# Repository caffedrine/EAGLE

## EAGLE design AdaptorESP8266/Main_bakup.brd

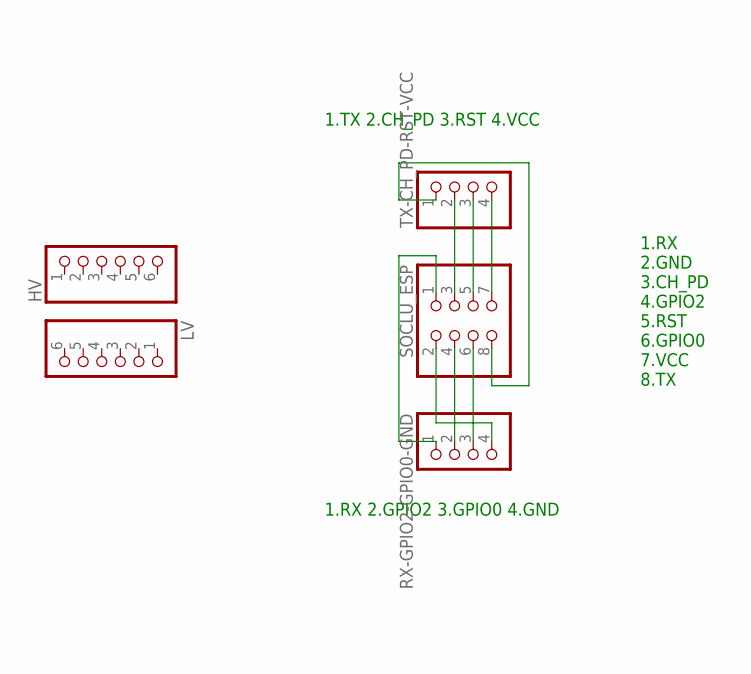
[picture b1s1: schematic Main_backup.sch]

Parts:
HV: PINHD-1X6; 1X06
LV: PINHD-1X6; 1X06
RX-GPIO2-GPIO0-GND: PINHD-1X4; 1X04
SOCLU_ESP: PINHD-2X4; 2X04
TX-CH_PD-RST-VCC: PINHD-1X4; 1X04

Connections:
unnamed: SOCLU_ESP.7, TX-CH_PD-RST-VCC.4
unnamed: SOCLU_ESP.5, TX-CH_PD-RST-VCC.3
unnamed: SOCLU_ESP.3, TX-CH_PD-RST-VCC.2
unnamed: SOCLU_ESP.8, TX-CH_PD-RST-VCC.1
unnamed: RX-GPIO2-GPIO0-GND.1, SOCLU_ESP.1
unnamed: RX-GPIO2-GPIO0-GND.4, SOCLU_ESP.2
unnamed: RX-GPIO2-GPIO0-GND.3, SOCLU_ESP.6
unnamed: RX-GPIO2-GPIO0-GND.2, SOCLU_ESP.4

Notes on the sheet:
1.RX 2.GND 3.CH_PD 4.GPIO2 5.RST 6.GPIO0 7.VCC 8.TX
1.TX 2.CH_PD 3.RST 4.VCC
1.RX 2.GPIO2 3.GPIO0 4.GND

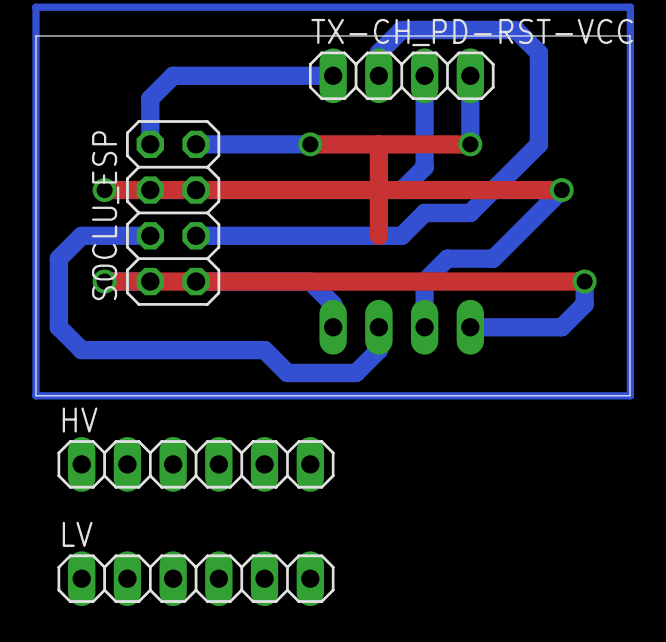
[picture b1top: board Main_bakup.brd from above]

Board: 2 copper layers, 33.0 x 20.0 mm, 5 parts (1 on the bottom side), 8 nets.

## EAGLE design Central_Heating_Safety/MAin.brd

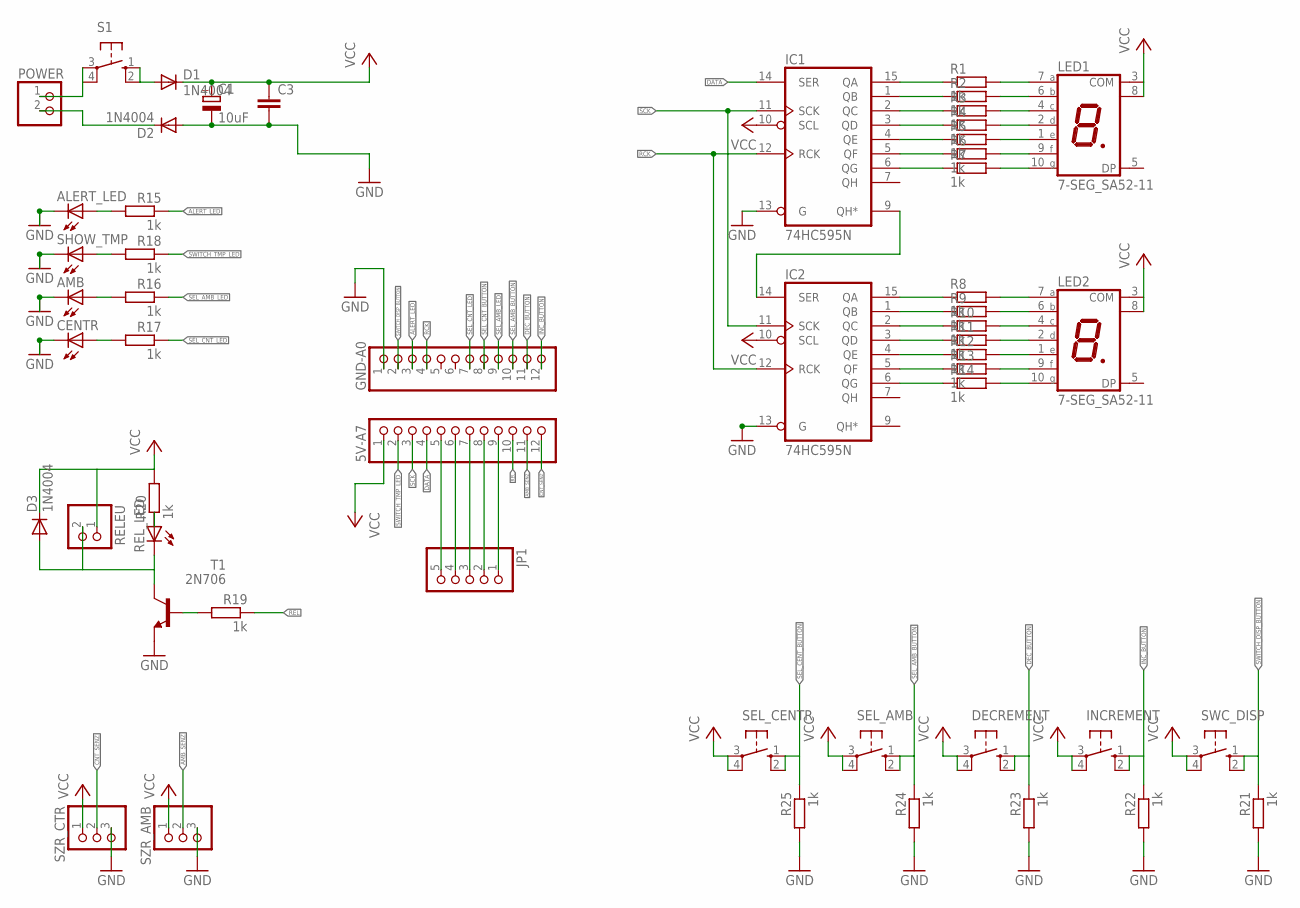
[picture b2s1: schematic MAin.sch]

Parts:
5V-A7: PINHD-1X12; 1X12
ALERT_LED: LED5MM
AMB: LED5MM
C1: 10uF; E2-5
C3: C-EU025-024X044; C025-024X044
CENTR: LED5MM
D1, D2, D3: 1N4004; DO41-10
DECREMENT: 40-XX; B3F-40XX
GND-A0: PINHD-1X12; 1X12
IC1, IC2: 74HC595N; DIL16
INCREMENT: 40-XX; B3F-40XX
JP1: PINHD-1X5; 1X05
LED1, LED2: 7-SEG_SA52-11; SA52-11
POWER: PINHD-1X2; 1X02
R1, R2, R3, R4, R5, R6, R7, R8, R9, R10, R11, R12, R13, R14, R15, R16, R17, R18, R19, R20, R21, R22, R23, R24, R25: 1k; 0309/12
RELEU: PINHD-1X2; 1X02
REL_LED: LED5MM
S1: 10-XX; B3F-10XX
SEL_AMB: 40-XX; B3F-40XX
SEL_CENTR: 40-XX; B3F-40XX
SHOW_TMP: LED5MM
SWC_DISP: 40-XX; B3F-40XX
SZR_AMB: PINHD-1X3; 1X03
SZR_CTR: PINHD-1X3; 1X03
T1: 2N706; TO18

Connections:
ALERT_LED: GND-A0.3, R15.1
AMB_SENZ: 5V-A7.11, SZR_AMB.2
CNT_SENZ: 5V-A7.12, SZR_CTR.2
DATA: 5V-A7.4, IC1.14 (SER)
DEC_BUTTON: DECREMENT.1 (S), DECREMENT.2 (S1), GND-A0.11, R23.1
GND: ALERT_LED.K (C), AMB.K (C), C1.-, C3.2, CENTR.K (C), D2.A, GND-A0.1, IC1.8 (GND), IC1.13 (G), IC2.8 (GND), IC2.13 (G), R21.2, R22.2, R23.2, R24.2, R25.2, SHOW_TMP.K (C), SZR_AMB.3, SZR_CTR.3, T1.1 (E)
INC_BUTTON: GND-A0.12, INCREMENT.1 (S), INCREMENT.2 (S1), R22.1
unnamed: LED1.7 (A), R1.2
unnamed: LED1.6 (B), R2.2
unnamed: LED1.4 (C), R3.2
unnamed: LED1.2 (D), R4.2
unnamed: LED1.1 (E), R5.2
unnamed: LED1.9 (F), R6.2
unnamed: LED1.10 (G), R7.2
unnamed: LED2.7 (A), R8.2
unnamed: LED2.6 (B), R9.2
unnamed: LED2.4 (C), R10.2
unnamed: LED2.2 (D), R11.2
unnamed: LED2.1 (E), R12.2
unnamed: LED2.9 (F), R13.2
unnamed: LED2.10 (G), R14.2
unnamed: IC1.15 (QA), R1.1
unnamed: IC1.1 (QB), R2.1
unnamed: IC1.2 (QC), R3.1
unnamed: IC1.3 (QD), R4.1
unnamed: IC1.4 (QE), R5.1
unnamed: IC1.5 (QF), R6.1
unnamed: IC1.6 (QG), R7.1
unnamed: IC2.15 (QA), R8.1
unnamed: IC2.1 (QB), R9.1
unnamed: IC2.2 (QC), R10.1
unnamed: IC2.3 (QD), R11.1
unnamed: IC2.4 (QE), R12.1
unnamed: IC2.5 (QF), R13.1
unnamed: IC2.6 (QG), R14.1
unnamed: IC1.9 (QH*), IC2.14 (SER)
unnamed: 5V-A7.9, JP1.1
unnamed: 5V-A7.8, JP1.2
unnamed: 5V-A7.7, JP1.3
unnamed: 5V-A7.6, JP1.4
unnamed: 5V-A7.5, JP1.5
unnamed: D1.A, S1.1 (S), S1.2 (S1)
unnamed: POWER.1, S1.3, S1.4 (P1)
unnamed: ALERT_LED.A, R15.2
unnamed: D2.C, POWER.2
unnamed: R20.1, REL_LED.A
unnamed: R19.2, T1.2 (B)
unnamed: AMB.A, R16.2
unnamed: CENTR.A, R17.2
unnamed: R18.2, SHOW_TMP.A
unnamed: D3.A, RELEU.2, REL_LED.K (C), T1.3 (C)
RCK: GND-A0.4, IC1.12 (RCK), IC2.12 (RCK)
REL: 5V-A7.10, R19.1
SCK: 5V-A7.3, IC1.11 (SCK), IC2.11 (SCK)
SEL_AMB_BUTTON: GND-A0.10, R24.1, SEL_AMB.1 (S), SEL_AMB.2 (S1)
SEL_AMB_LED: GND-A0.9, R16.1
SEL_CENT_BUTTON: GND-A0.7, R25.1, SEL_CENTR.1 (S), SEL_CENTR.2 (S1)
SEL_CNT_BUTTON: GND-A0.8
SEL_CNT_LED: R17.1
SWITCH_DISP_BUTTON: GND-A0.2, R21.1, SWC_DISP.1 (S), SWC_DISP.2 (S1)
SWITCH_TMP_LED: 5V-A7.2, R18.1
VCC: 5V-A7.1, C1.+, C3.1, D1.C, D3.C, DECREMENT.3, DECREMENT.4 (P1), IC1.10 (SCL), IC1.16 (VCC), IC2.10 (SCL), IC2.16 (VCC), INCREMENT.3, INCREMENT.4 (P1), LED1.3 (COM), LED1.8 (COM), LED2.3 (COM), LED2.8 (COM), R20.2, RELEU.1, SEL_AMB.3, SEL_AMB.4 (P1), SEL_CENTR.3, SEL_CENTR.4 (P1), SWC_DISP.3, SWC_DISP.4 (P1), SZR_AMB.1, SZR_CTR.1

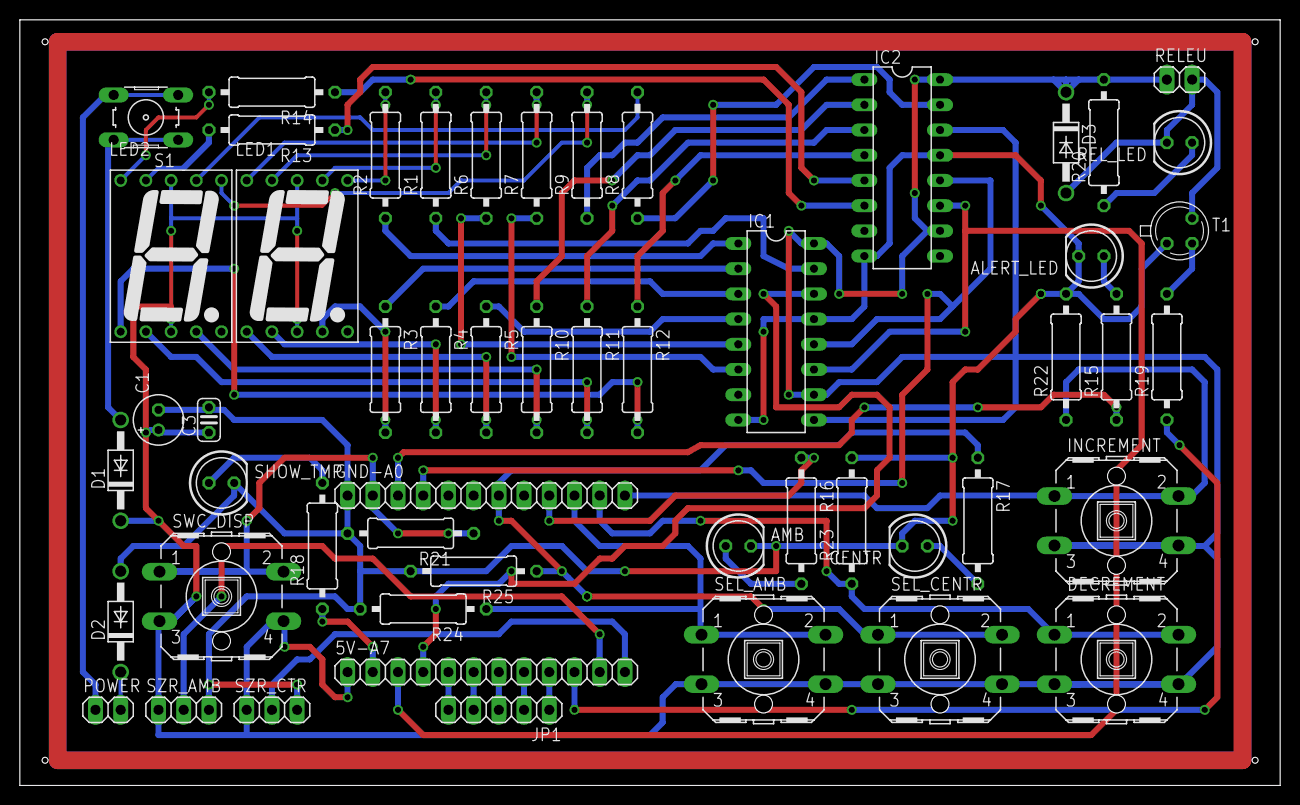
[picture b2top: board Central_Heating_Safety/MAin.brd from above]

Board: 2 copper layers, 127.0 x 77.1 mm, 53 parts (0 on the bottom side), 60 nets.

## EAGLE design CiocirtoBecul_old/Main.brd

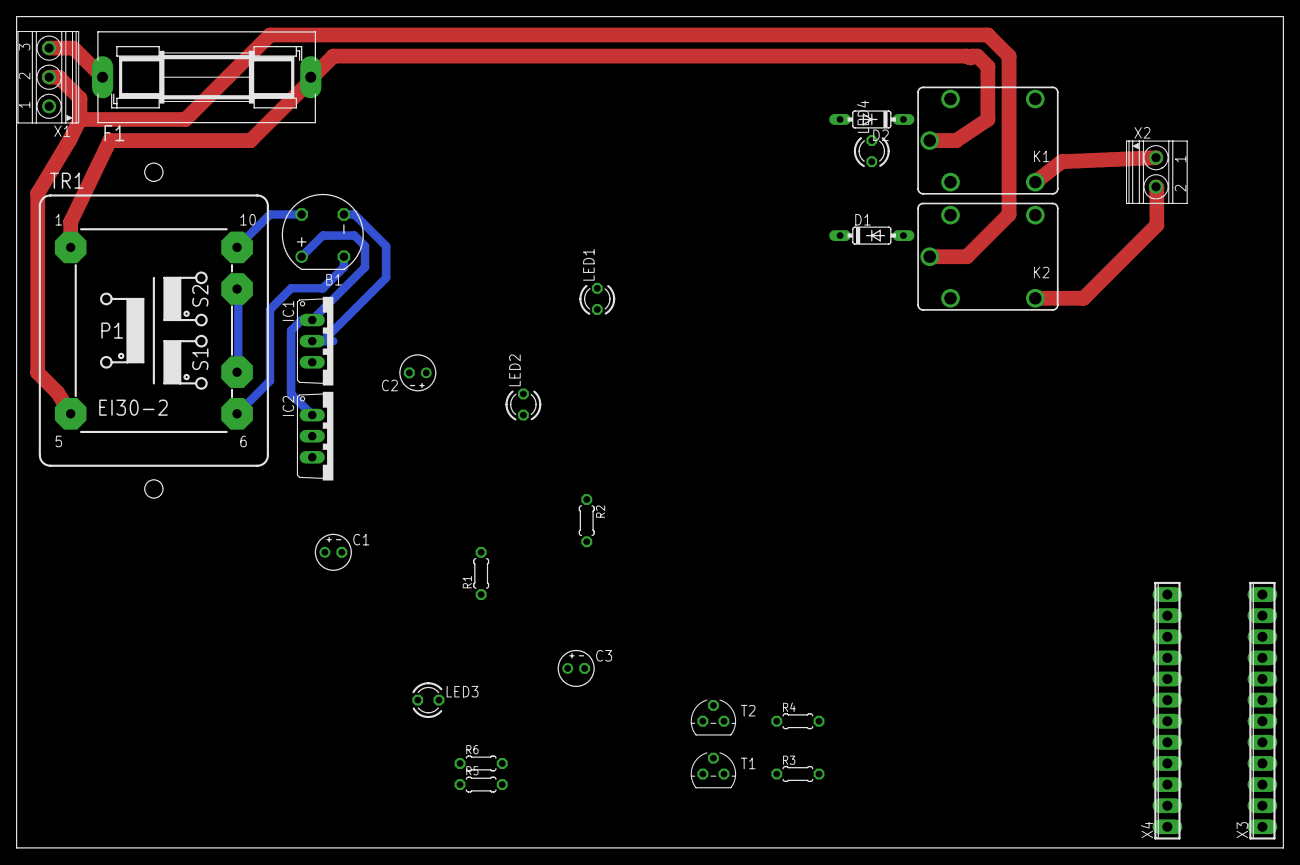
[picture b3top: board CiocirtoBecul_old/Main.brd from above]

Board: 2 copper layers, 152.4 x 100.0 mm, 28 parts (0 on the bottom side), 21 nets.

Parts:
B1: RB1A
C1, C2, C3: 22uf; E2-4
D1, D2: 1N4148DO35-7; DO35-7
F1: SH25
IC1: 7805TV; TO220V
IC2: 7812TV; TO220V
K1, K2: CQ1-12V; CQ1
LED1, LED2, LED3, LED4: TLLG4400; LED3MM
R1, R2, R3, R4, R5, R6: 1; 0204/5
T1, T2: BC547; TO92
TR1: EI30-2
X1: 1751251
X2: 1751248
X3, X4: 12POL254

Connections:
+5V: C2.+, IC1.3, R1.2
+12V: C3.+, D1.C, D2.C, IC2.3, K1.1, K2.1, R2.2, R5.2, R6.2
GND: B1.-, C1.-, C2.-, C3.-, IC1.2, IC2.2, LED1.K, LED2.K, T1.1, T2.1
unnamed: F1.2, K1.C, TR1.1
unnamed: K2.C, TR1.5, X1.2
unnamed: K1.NO, X2.1
unnamed: K2.NO, X2.2
unnamed: TR1.7, TR1.9
unnamed: B1.AC1, TR1.10
unnamed: B1.AC2, TR1.6
unnamed: B1.+, C1.+, IC1.1, IC2.1
unnamed: D1.A, K2.2, LED3.K, T1.3
unnamed: LED2.A, R2.1
unnamed: LED3.A, R5.1
unnamed: D2.A, K1.2, LED4.K, T2.3
unnamed: LED1.A, R1.1
unnamed: R3.1, T1.2
unnamed: R4.1, T2.2
unnamed: R3.2, R4.2
unnamed: F1.1, X1.3
unnamed: LED4.A, R6.1

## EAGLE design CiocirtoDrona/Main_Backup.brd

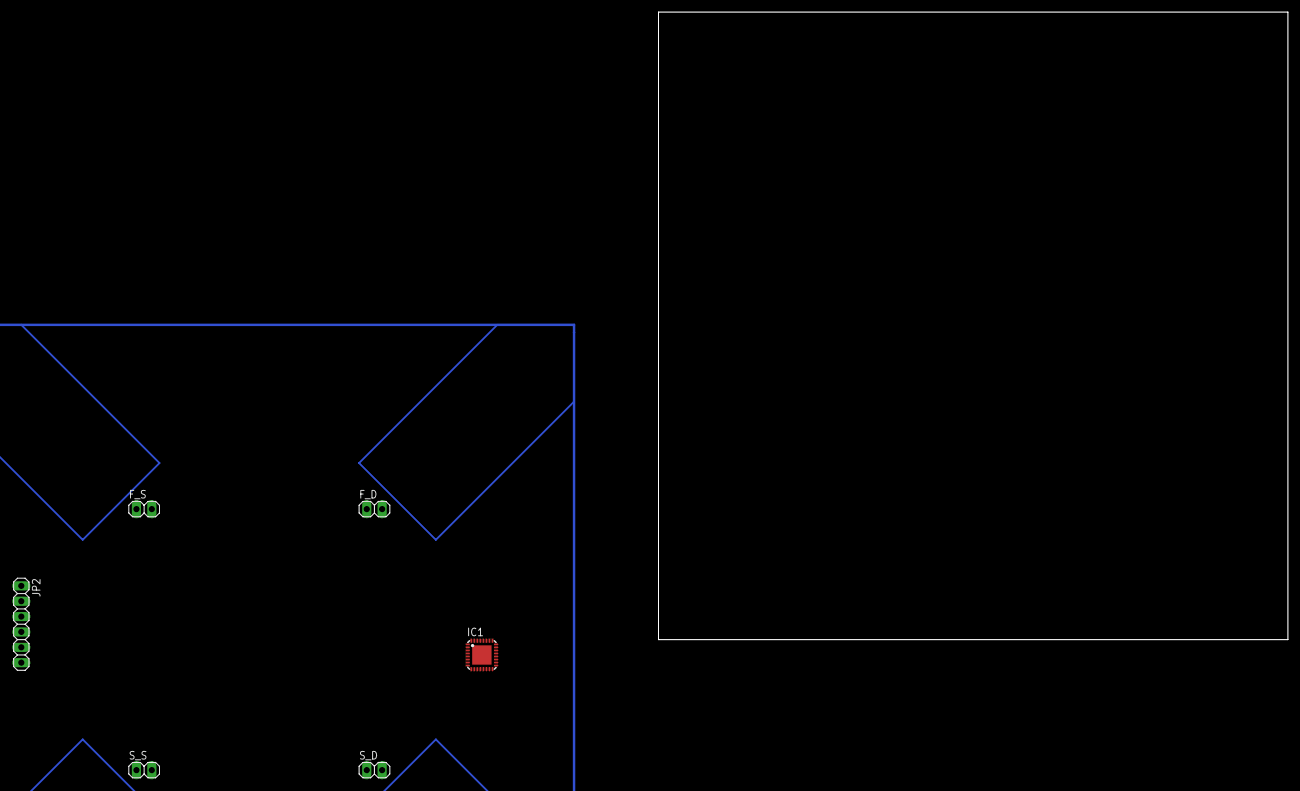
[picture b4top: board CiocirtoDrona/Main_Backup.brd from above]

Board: 2 copper layers, 104.1 x 103.8 mm, 6 parts (0 on the bottom side), 2 nets.

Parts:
F_D: 1X02
F_S: 1X02
IC1: MEGA8-MI; MLF32-TH
JP2: 1X06
S_D: 1X02
S_S: 1X02

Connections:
GND: IC1.3, IC1.5, IC1.21
VCC: IC1.4, IC1.6

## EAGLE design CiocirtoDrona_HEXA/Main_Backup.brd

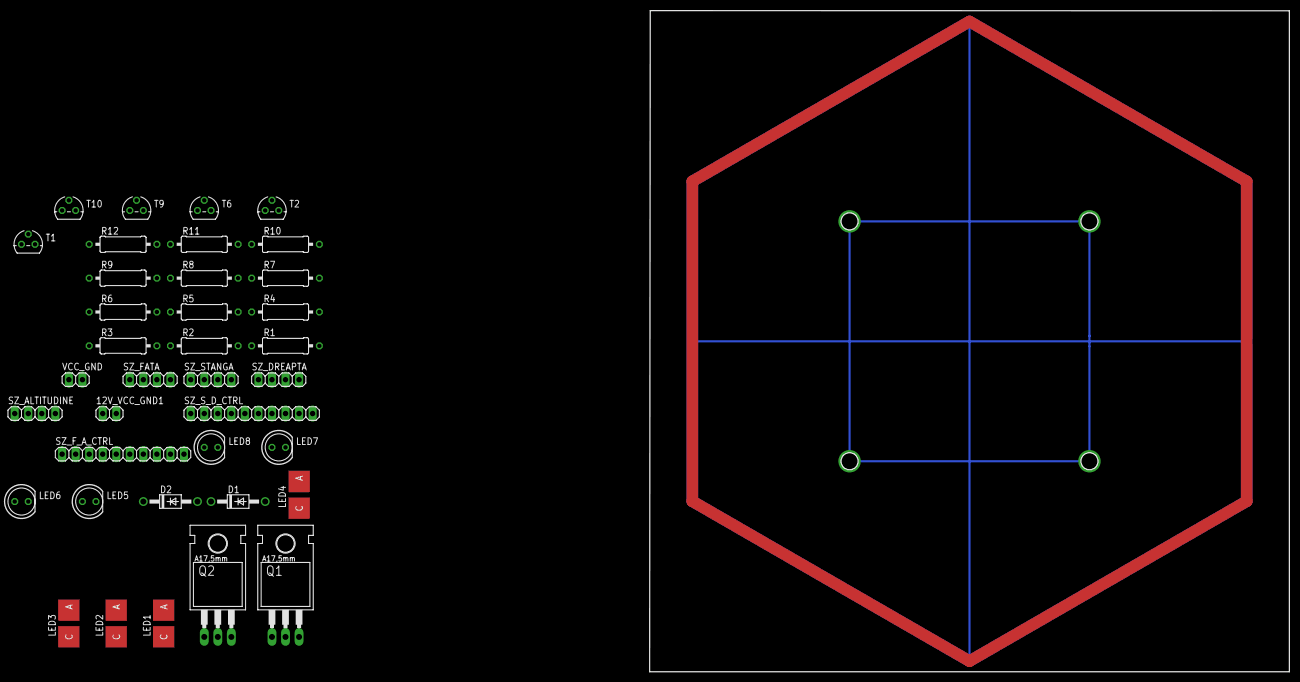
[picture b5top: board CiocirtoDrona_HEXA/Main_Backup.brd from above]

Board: 2 copper layers, 120.0 x 124.0 mm, 37 parts (0 on the bottom side), 30 nets.

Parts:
12V_VCC_GND1: 1X02
D1, D2: 1N4004; DO41-10
LED1, LED2, LED3, LED4: 1W; OSRAM-SIDELED
LED5, LED6, LED7, LED8: LED5MM
Q1, Q2: IRFZ48Z; TO220BH
R1: 10Ohm5W; 0309/12
R2: 3Ohm; 0309/12
R3: 1Ohm; 0309/12
R4, R6, R7, R8, R9, R10, R11, R12: 1K; 0309/12
R5: 14.3Ohm; 0309/12
SZ_ALTITUDINE: 1X04
SZ_DREAPTA: 1X04
SZ_FATA: 1X04
SZ_F_A_CTRL: 1X10
SZ_STANGA: 1X04
SZ_S_D_CTRL: 1X10
T1, T2, T6, T9, T10: BC547; TO92
VCC_GND: 1X02

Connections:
GND: D1.A, D2.A, Q1.S, Q2.S, R3.2, SZ_ALTITUDINE.4, SZ_DREAPTA.4, SZ_FATA.4, SZ_F_A_CTRL.3, SZ_F_A_CTRL.4, SZ_STANGA.4, SZ_S_D_CTRL.3, SZ_S_D_CTRL.4, T6.1
unnamed: SZ_FATA.2, SZ_F_A_CTRL.7
unnamed: D1.C, VCC_GND.2
unnamed: SZ_FATA.3, SZ_F_A_CTRL.10
unnamed: SZ_ALTITUDINE.2, SZ_F_A_CTRL.6
unnamed: SZ_ALTITUDINE.3, SZ_F_A_CTRL.9
unnamed: SZ_DREAPTA.2, SZ_S_D_CTRL.7
unnamed: SZ_DREAPTA.3, SZ_S_D_CTRL.10
unnamed: SZ_STANGA.2, SZ_S_D_CTRL.6
unnamed: SZ_STANGA.3, SZ_S_D_CTRL.9
unnamed: SZ_ALTITUDINE.1, SZ_FATA.1, SZ_F_A_CTRL.2, T9.1
unnamed: SZ_DREAPTA.1, SZ_STANGA.1, SZ_S_D_CTRL.2, T10.1
unnamed: LED1.C, LED2.C, LED3.C, LED4.C, Q2.D
unnamed: LED1.A, LED2.A, LED3.A, LED4.A, R1.1, R12.2
unnamed: Q2.G, T1.1
unnamed: R1.2, R2.1, R3.1
unnamed: 12V_VCC_GND1.2, D2.C
unnamed: LED5.K, LED6.K, LED7.K, LED8.K, T6.3
unnamed: LED5.A, LED6.A, LED7.A, LED8.A, R4.2
unnamed: Q1.D, R5.2, R11.2
unnamed: R6.2, T6.2
unnamed: R7.2, T1.2
unnamed: R8.2, T9.2
unnamed: R9.2, T10.2
unnamed: R10.2, T2.2
unnamed: R12.1, T1.3
unnamed: R11.1, T2.3
unnamed: Q1.G, T2.1
VCC: R4.1, T9.3, T10.3, VCC_GND.1
VEE: 12V_VCC_GND1.1, R2.2, R5.1
